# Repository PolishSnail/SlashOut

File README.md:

# SlashOut
96% custom keyboard with detachable numpad section

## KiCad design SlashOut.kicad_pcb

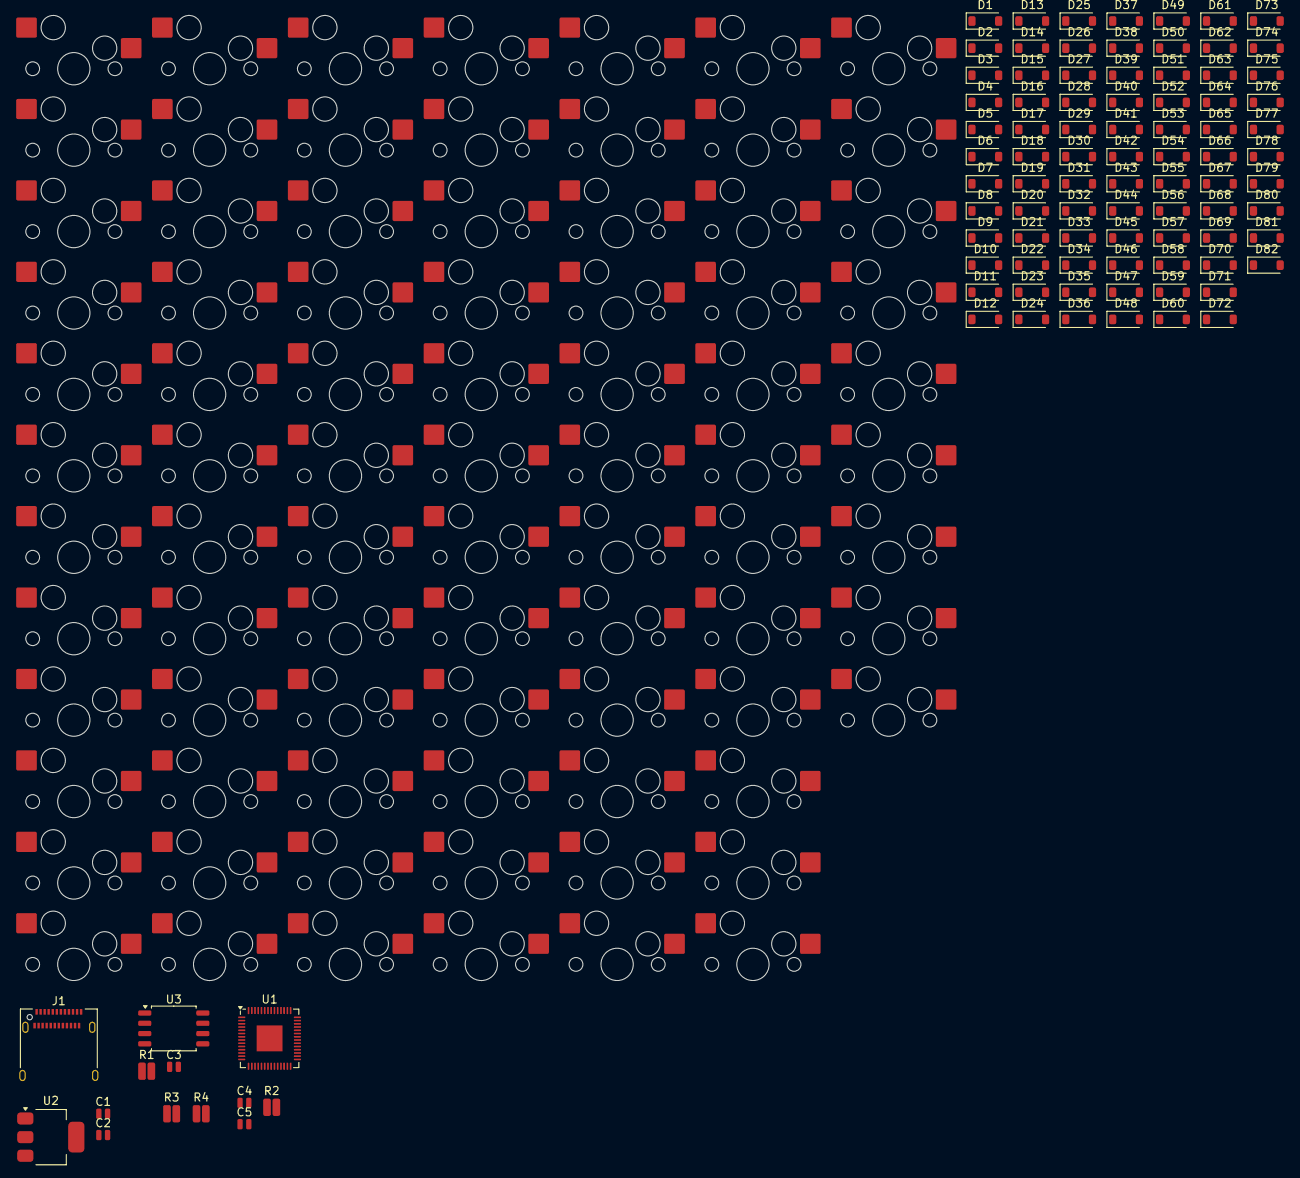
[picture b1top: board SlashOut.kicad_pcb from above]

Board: 2 copper layers, 176 parts (0 on the bottom side), 114 nets, no tracks yet.

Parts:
C1, C2: 10u; C_0504_1310Metric
C3: 100n; C_0504_1310Metric
C4, C5: 15p; C_0504_1310Metric
D1, D2, D3, D4, D5, D6, D7, D8, D9, D10, D11, D12, D13, D14, D15, D16, D17, D18, D19, D20, D21, D22, D23, D24, D25, D26, D27, D28, D29, D30, D31, D32, D33, D34, D35, D36, D37, D38, D39, D40, D41, D42, D43, D44, D45, D46, D47, D48, D49, D50, D51, D52, D53, D54, D55, D56, D57, D58, D59, D60, D61, D62, D63, D64, D65, D66, D67, D68, D69, D70, D71, D72, D73, D74, D75, D76, D77, D78, D79, D80, D81, D82: 1N4148W; D_SOD-123
J1: USB_C_Receptacle_USB2.0_14P; USB_C_Receptacle_Amphenol_12401610E4-2A
R1: 1K; R_0508_1220Metric
R2: 1k; R_0508_1220Metric
R3, R4: 27; R_0508_1220Metric
SW1, SW2, SW3, SW4, SW5, SW6, SW7, SW8, SW9, SW10, SW11, SW12, SW13, SW14, SW15, SW16, SW17, SW18, SW19, SW20, SW21, SW22, SW23, SW24, SW25, SW26, SW27, SW28, SW29, SW30, SW31, SW32, SW33, SW34, SW35, SW36, SW37, SW38, SW39, SW40, SW41, SW42, SW43, SW44, SW45, SW46, SW47, SW48, SW49, SW50, SW51, SW52, SW53, SW54, SW55, SW56, SW57, SW58, SW59, SW60, SW61, SW62, SW63, SW64, SW65, SW66, SW67, SW68, SW69, SW70, SW71, SW72, SW73, SW74, SW75, SW76, SW77, SW78, SW79, SW80, SW81: SW_Push_45deg; MX-Hotswap-1U
U1: RP2040; QFN-56-1EP_7x7mm_P0.4mm_EP3.2x3.2mm
U2: NCP1117-3.3_SOT223; SOT-223-3_TabPin2
U3: W25Q128JVS; SOIC-8_5.3x5.3mm_P1.27mm

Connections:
+3V3: C2.1, U2.2 (VO)
/Keyboard Matrix/COL1: SW16.1, SW31.1, SW46.1, SW60.1, SW74.1
/Keyboard Matrix/COL2: SW1.1, SW17.1, SW32.1, SW47.1, SW61.1, SW75.1
/Keyboard Matrix/COL3: SW2.1, SW18.1, SW33.1, SW48.1, SW62.1, SW76.1
/Keyboard Matrix/COL4: SW3.1, SW19.1, SW34.1, SW49.1, SW63.1, SW77.1
/Keyboard Matrix/COL5: SW4.1, SW20.1, SW35.1, SW50.1, SW64.1, SW78.1
/Keyboard Matrix/COL6: SW5.1, SW21.1, SW36.1, SW51.1, SW65.1, SW79.1
/Keyboard Matrix/COL7: SW6.1, SW22.1, SW37.1, SW52.1, SW66.1, SW80.1
/Keyboard Matrix/COL8: SW7.1, SW23.1, SW38.1, SW53.1, SW67.1, SW81.1
/Keyboard Matrix/COL9: SW8.1, SW24.1, SW39.1, SW54.1, SW68.1
/Keyboard Matrix/COL10: SW9.1, SW25.1, SW40.1, SW55.1, SW69.1
/Keyboard Matrix/COL11: SW10.1, SW26.1, SW41.1, SW56.1, SW70.1
/Keyboard Matrix/COL12: SW11.1, SW27.1, SW42.1, SW57.1, SW71.1
/Keyboard Matrix/COL13: SW12.1, SW28.1, SW43.1, SW58.1, SW72.1
/Keyboard Matrix/COL14: SW13.1, SW29.1, SW44.1, SW59.1, SW73.1
/Keyboard Matrix/COL15: SW14.1, SW30.1, SW45.1
/Keyboard Matrix/ROW1: D1.1 (K), D2.1 (K), D3.1 (K), D4.1 (K), D5.1 (K), D6.1 (K), D7.1 (K), D8.1 (K), D9.1 (K), D10.1 (K), D11.1 (K), D12.1 (K), D13.1 (K), D14.1 (K), D15.1 (K), D82.1 (K)
/Keyboard Matrix/ROW2: D16.1 (K), D17.1 (K), D18.1 (K), D19.1 (K), D20.1 (K), D21.1 (K), D22.1 (K), D23.1 (K), D24.1 (K), D25.1 (K), D26.1 (K), D27.1 (K), D28.1 (K), D29.1 (K), D30.1 (K)
/Keyboard Matrix/ROW3: D31.1 (K), D32.1 (K), D33.1 (K), D34.1 (K), D35.1 (K), D36.1 (K), D37.1 (K), D38.1 (K), D39.1 (K), D40.1 (K), D41.1 (K), D42.1 (K), D43.1 (K), D44.1 (K), D45.1 (K)
/Keyboard Matrix/ROW4: D46.1 (K), D47.1 (K), D48.1 (K), D49.1 (K), D50.1 (K), D51.1 (K), D52.1 (K), D53.1 (K), D54.1 (K), D55.1 (K), D56.1 (K), D57.1 (K), D58.1 (K), D59.1 (K)
/Keyboard Matrix/ROW5: D60.1 (K), D61.1 (K), D62.1 (K), D63.1 (K), D64.1 (K), D65.1 (K), D66.1 (K), D67.1 (K), D68.1 (K), D69.1 (K), D70.1 (K), D71.1 (K), D72.1 (K), D73.1 (K)
/Keyboard Matrix/ROW6: D74.1 (K), D75.1 (K), D76.1 (K), D77.1 (K), D78.1 (K), D79.1 (K), D80.1 (K), D81.1 (K)
/MCU/Memory/QSPI_SS: R1.1, U3.1 (~CS)
/MCU/USB + Power/USB_D+: J1.A6 (D+), J1.B6 (D+)
/MCU/USB + Power/USB_D-: J1.A7 (D-), J1.B7 (D-)
GND: C1.2, C2.2, C3.2, C4.2, C5.2, J1.A1 (GND), J1.A12 (GND), J1.B1 (GND), J1.B12 (GND), J1.S1 (SHIELD), U2.1 (GND), U3.4 (GND)
unnamed: C5.1, R2.2
unnamed: D1.2 (A), SW1.2
unnamed: D2.2 (A), SW2.2
unnamed: D3.2 (A), SW3.2
unnamed: D4.2 (A), SW4.2
unnamed: D5.2 (A), SW5.2
unnamed: D6.2 (A), SW6.2
unnamed: D7.2 (A), SW7.2
unnamed: D8.2 (A), SW8.2
unnamed: D9.2 (A), SW9.2
unnamed: D10.2 (A), SW10.2
unnamed: D11.2 (A), SW11.2
unnamed: D12.2 (A), SW12.2
unnamed: D13.2 (A), SW13.2
unnamed: D14.2 (A), SW14.2
unnamed: D15.2 (A), SW15.2
unnamed: D16.2 (A), SW16.2
unnamed: D17.2 (A), SW17.2
unnamed: D18.2 (A), SW18.2
unnamed: D19.2 (A), SW19.2
unnamed: D20.2 (A), SW20.2
unnamed: D21.2 (A), SW21.2
unnamed: D22.2 (A), SW22.2
unnamed: D23.2 (A), SW23.2
unnamed: D24.2 (A), SW24.2
unnamed: D25.2 (A), SW25.2
unnamed: D26.2 (A), SW26.2
unnamed: D27.2 (A), SW27.2
unnamed: D28.2 (A), SW28.2
unnamed: D29.2 (A), SW29.2
unnamed: D30.2 (A), SW30.2
unnamed: D31.2 (A), SW31.2
unnamed: D32.2 (A), SW32.2
unnamed: D33.2 (A), SW33.2
unnamed: D34.2 (A), SW34.2
unnamed: D35.2 (A), SW35.2
unnamed: D36.2 (A), SW36.2
unnamed: D37.2 (A), SW37.2
unnamed: D38.2 (A), SW38.2
unnamed: D39.2 (A), SW39.2
unnamed: D40.2 (A), SW40.2
unnamed: D41.2 (A), SW41.2
unnamed: D42.2 (A), SW42.2
unnamed: D43.2 (A), SW43.2
unnamed: D44.2 (A), SW44.2
unnamed: D45.2 (A), SW45.2
unnamed: D46.2 (A), SW46.2
unnamed: D47.2 (A), SW47.2
unnamed: D48.2 (A), SW48.2
unnamed: D49.2 (A), SW49.2
unnamed: D50.2 (A), SW50.2
unnamed: D51.2 (A), SW51.2
unnamed: D52.2 (A), SW52.2
unnamed: D53.2 (A), SW53.2
unnamed: D54.2 (A), SW54.2
unnamed: D55.2 (A), SW55.2
unnamed: D56.2 (A), SW56.2
unnamed: D57.2 (A), SW57.2
unnamed: D58.2 (A), SW58.2
unnamed: D59.2 (A), SW59.2
unnamed: D60.2 (A), SW60.2
unnamed: D61.2 (A), SW61.2
unnamed: D62.2 (A), SW62.2
unnamed: D63.2 (A), SW63.2
unnamed: D64.2 (A), SW64.2
unnamed: D65.2 (A), SW65.2
unnamed: D66.2 (A), SW66.2
unnamed: D67.2 (A), SW67.2
unnamed: D68.2 (A), SW68.2
unnamed: D69.2 (A), SW69.2
unnamed: D70.2 (A), SW70.2
unnamed: D71.2 (A), SW71.2
unnamed: D72.2 (A), SW72.2
unnamed: D73.2 (A), SW73.2
unnamed: D74.2 (A), SW74.2
unnamed: D75.2 (A), SW75.2
unnamed: D76.2 (A), SW76.2
unnamed: D77.2 (A), SW77.2
unnamed: D78.2 (A), SW78.2
unnamed: D79.2 (A), SW79.2
unnamed: D80.2 (A), SW80.2
unnamed: D81.2 (A), SW81.2
unnamed: U1.23 (DVDD), U1.50 (DVDD)
unnamed: U1.1 (IOVDD), U1.10 (IOVDD), U1.22 (IOVDD), U1.33 (IOVDD), U1.42 (IOVDD), U1.49 (IOVDD)
unnamed: R4.1, U1.46 (USB_DM)
unnamed: R3.1, U1.47 (USB_DP)
unnamed: C3.1, U3.8 (VCC)
VBUS: C1.1, J1.A4 (VBUS), J1.A9 (VBUS), J1.B4 (VBUS), J1.B9 (VBUS), U2.3 (VI)

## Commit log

2025-10-14 adding kicad files
2025-10-15 added oscillator and memory
2025-10-16 adding labels and updating PCB
2025-10-30 Added potentially better Japanese Duplex Matrix
